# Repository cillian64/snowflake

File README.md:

# Snowflake: David's "Yuletronics" project.

A christmas decoration shaped like a snowflake, with beautiful white LEDs.
Also the most ridiculously shaped PCB I've ever had made.

Uses the TI TLV61220 boost SMPS controller to generate 5V from a single
alkaline cell.  Alternatively powered via MicroUSB-B.  Controlled by STM32F042,
programmed using TagConnect SWD or USB DFU.

Based on [Adam Greig's Christmas
Tree](https://github.com/adamgreig/yuletronics/)

Made in [KiCAD 4.0.4](http://kicad-pcb.org/).

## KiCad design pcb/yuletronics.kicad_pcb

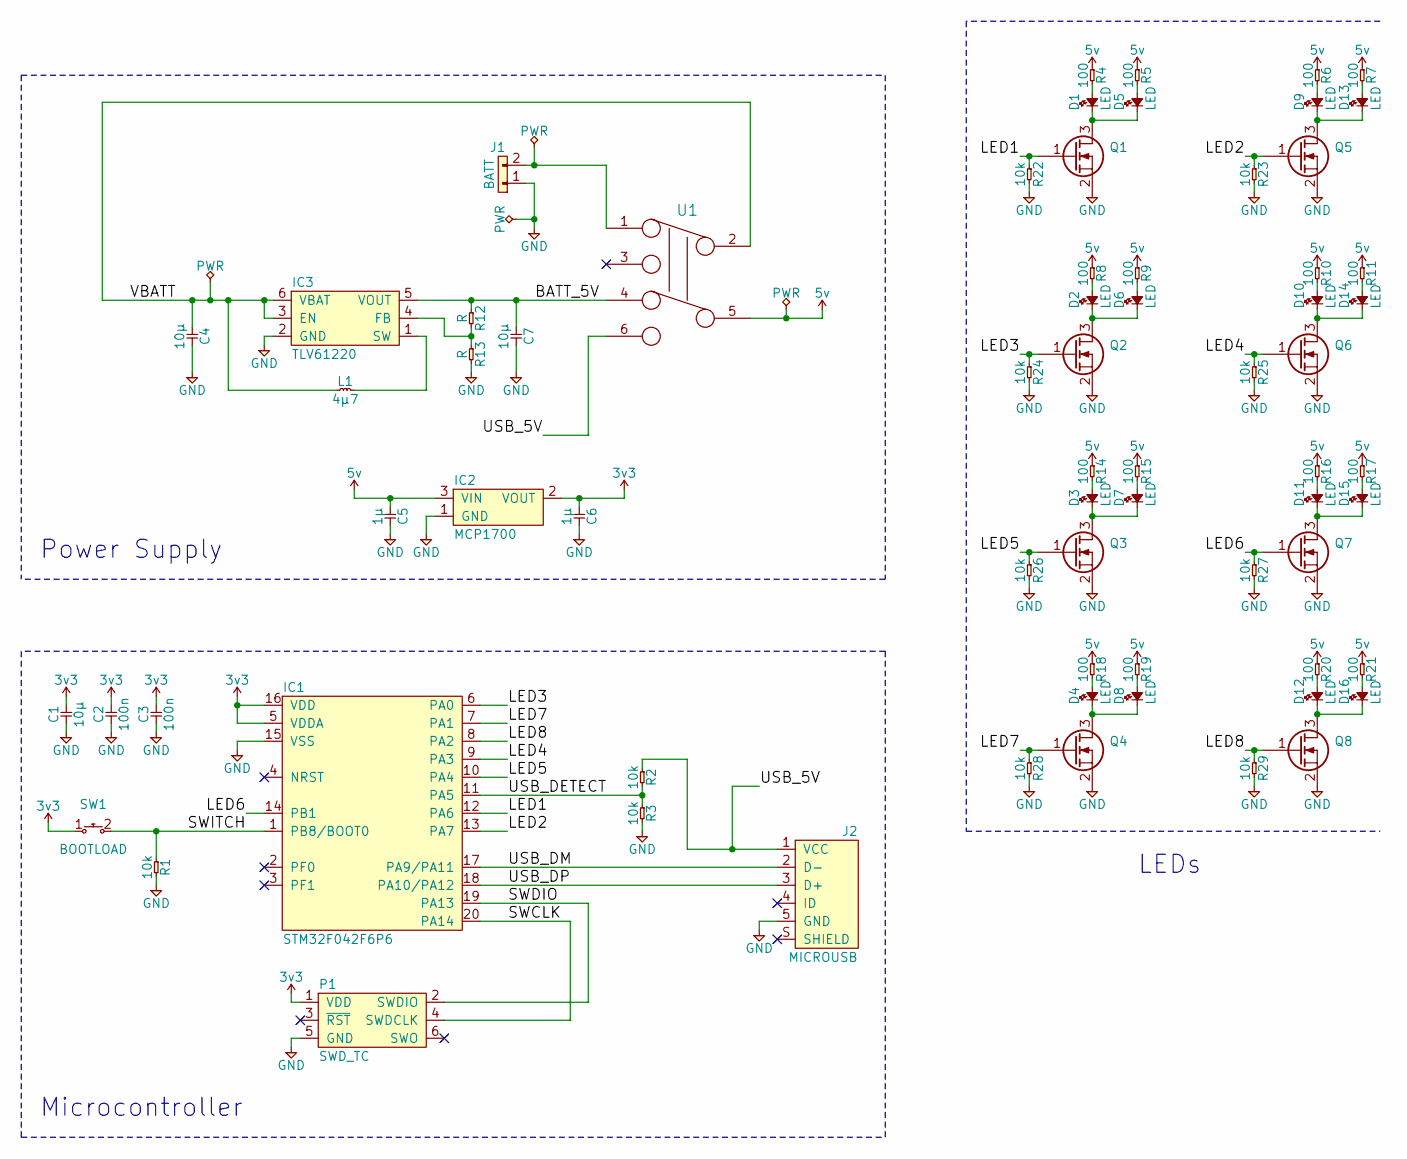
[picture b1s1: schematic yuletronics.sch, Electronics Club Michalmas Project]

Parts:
C1, C4, C7: 10µ; 0805; Farnell 2320851
C2, C3: 100n; 0805; Farnell 1759265
C5, C6: 1µ; 0805; Farnell 2320853
D1, D2, D3, D4, D5, D6, D7, D8, D9, D10, D11, D12, D13, D14, D15, D16: LED; 0805-LED; Farnell 1716764
IC1: STM32F042F6P6; TSSOP-20; Farnell 2469549
IC2: MCP1700; SOT-23; Farnell 1296592
IC3: TLV61220; SOT-23-6; Farnell 2323546
J1: BATT; AAA_HOLDER; Farnell 1702632
J2: MICROUSB; MICROUSB_MOLEX_47589-0001; Farnell 1568023
L1: 4µ7; 2016M; Farnell 2616849
P1: SWD_TC; TC2030-NL
Q1, Q2, Q3, Q4, Q5, Q6, Q7, Q8: BSS138P; SOT-23; Farnell 1859849
R1, R2, R3: 10k; 0805; Farnell 9332391
R4, R5, R6, R7, R8, R9, R10, R11, R14, R15, R16, R17, R18, R19, R20, R21: 100; 0805
R12, R13: R; 0805
R22, R23, R24, R25, R26, R27, R28, R29: 10k; 0805
SW1: BOOTLOAD; MOM_SWITCH; Farnell 2056809
U1: dpdt; Farnell 2435098

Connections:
3v3: C1.2, C2.2, C3.2, C6.1, IC1.5 (VDDA), IC1.16 (VDD), IC2.2 (VOUT), P1.1 (VDD), SW1.1
5v: C5.1, IC2.3 (VIN), R4.1, R5.1, R6.1, R7.1, R8.1, R9.1, R10.1, R11.1, R14.1, R15.1, R16.1, R17.1, R18.1, R19.1, R20.1, R21.1, U1.5
/BATT_5V: C7.1, IC3.5 (VOUT), R12.1, U1.4
/LED1: IC1.12 (PA6), Q1.1 (G), R22.1
/LED2: IC1.13 (PA7), Q5.1 (G), R23.1
/LED3: IC1.6 (PA0), Q2.1 (G), R24.1
/LED4: IC1.9 (PA3), Q6.1 (G), R25.1
/LED5: IC1.10 (PA4), Q3.1 (G), R26.1
/LED6: IC1.14 (PB1), Q7.1 (G), R27.1
/LED7: IC1.7 (PA1), Q4.1 (G), R28.1
/LED8: IC1.8 (PA2), Q8.1 (G), R29.1
/SWCLK: IC1.20 (PA14), P1.4 (SWDCLK)
/SWDIO: IC1.19 (PA13), P1.2 (SWDIO)
/SWITCH: IC1.1 (PB8/BOOT0), R1.1, SW1.2
/USB_5V: J2.1 (VCC), R2.1, U1.6
/USB_DETECT: IC1.11 (PA5), R2.2, R3.1
/USB_DM: IC1.17 (PA9/PA11), J2.2 (D-)
/USB_DP: IC1.18 (PA10/PA12), J2.3 (D+)
/VBATT: C4.1, IC3.3 (EN), IC3.6 (VBAT), L1.1, U1.2
GND: C1.1, C2.1, C3.1, C4.2, C5.2, C6.2, C7.2, IC1.15 (VSS), IC2.1 (GND), IC3.2 (GND), J1.1, J2.5 (GND), P1.5 (GND), Q1.2 (S), Q2.2 (S), Q3.2 (S), Q4.2 (S), Q5.2 (S), Q6.2 (S), Q7.2 (S), Q8.2 (S), R1.2, R3.2, R13.2, R22.2, R23.2, R24.2, R25.2, R26.2, R27.2, R28.2, R29.2
unnamed: D1.1, D5.1, Q1.3 (D)
unnamed: D1.2, R4.2
unnamed: D2.1, D6.1, Q2.3 (D)
unnamed: D2.2, R8.2
unnamed: D3.1, D7.1, Q3.3 (D)
unnamed: D3.2, R14.2
unnamed: D4.1, D8.1, Q4.3 (D)
unnamed: D4.2, R18.2
unnamed: D5.2, R5.2
unnamed: D6.2, R9.2
unnamed: D7.2, R15.2
unnamed: D8.2, R19.2
unnamed: D9.2, R6.2
unnamed: D10.1, D14.1, Q6.3 (D)
unnamed: D10.2, R10.2
unnamed: D11.1, D15.1, Q7.3 (D)
unnamed: D11.2, R16.2
unnamed: D12.1, D16.1, Q8.3 (D)
unnamed: D12.2, R20.2
unnamed: D9.1, D13.1, Q5.3 (D)
unnamed: D13.2, R7.2
unnamed: D14.2, R11.2
unnamed: D15.2, R17.2
unnamed: D16.2, R21.2
unnamed: IC3.1 (SW), L1.2
unnamed: IC3.4 (FB), R12.2, R13.1
unnamed: J1.2, U1.1

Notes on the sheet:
Power Supply
Microcontroller
LEDs

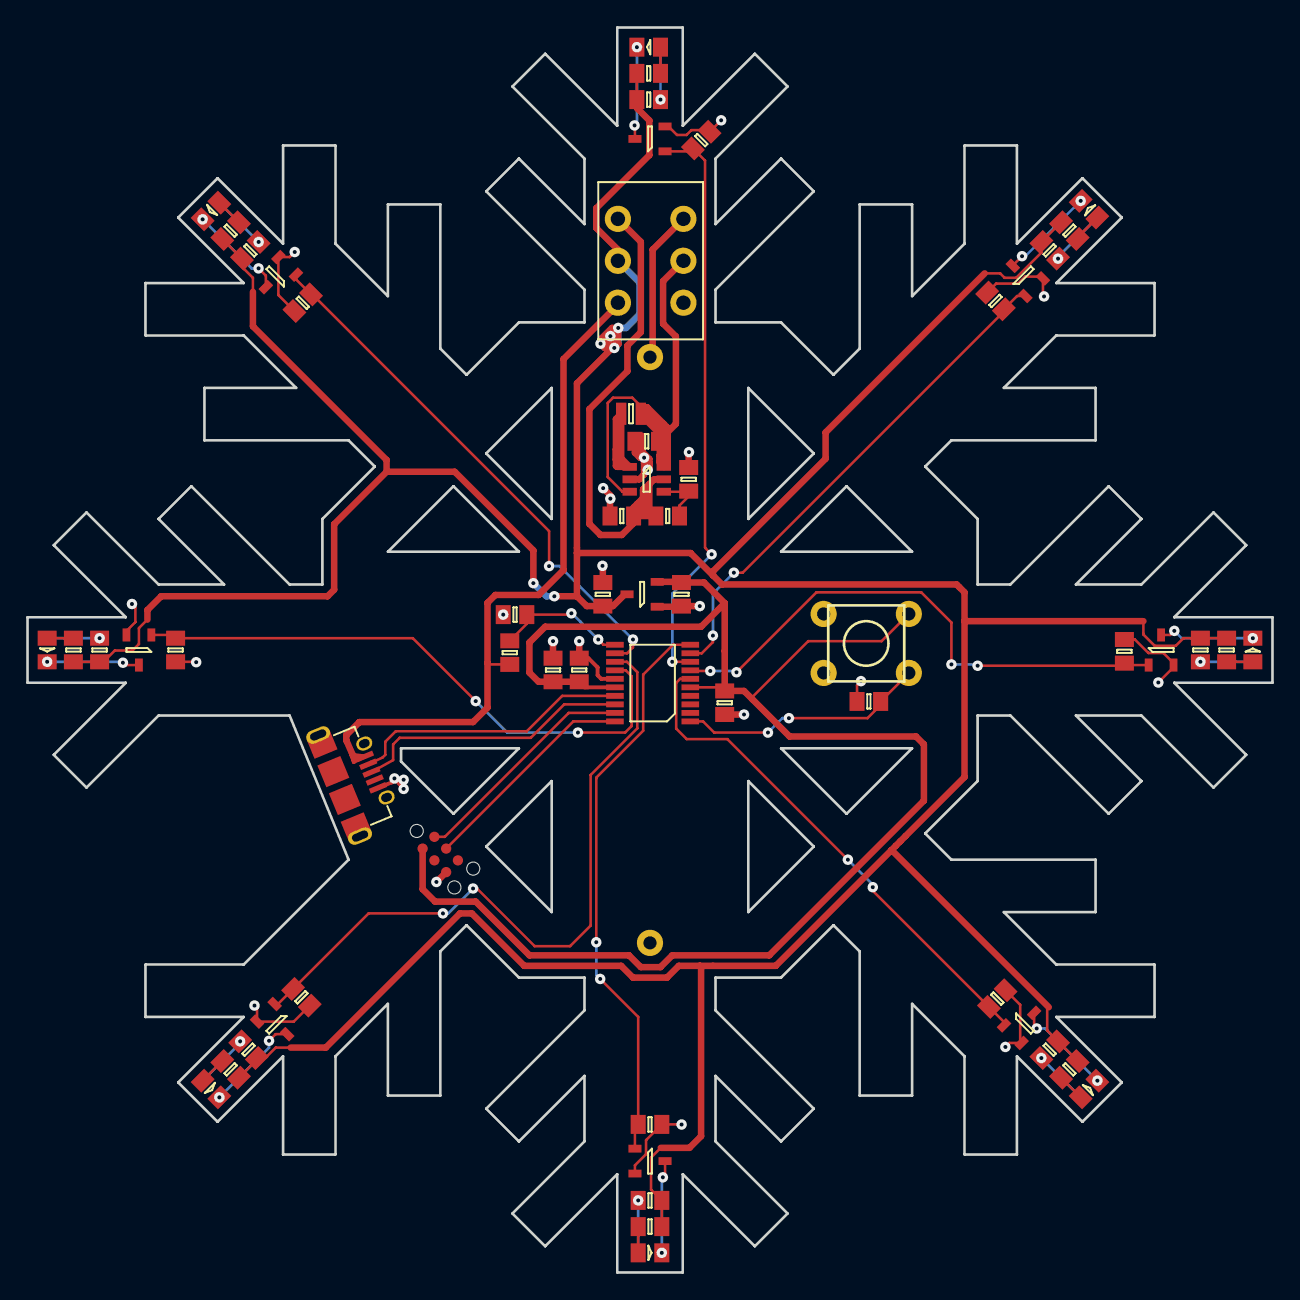
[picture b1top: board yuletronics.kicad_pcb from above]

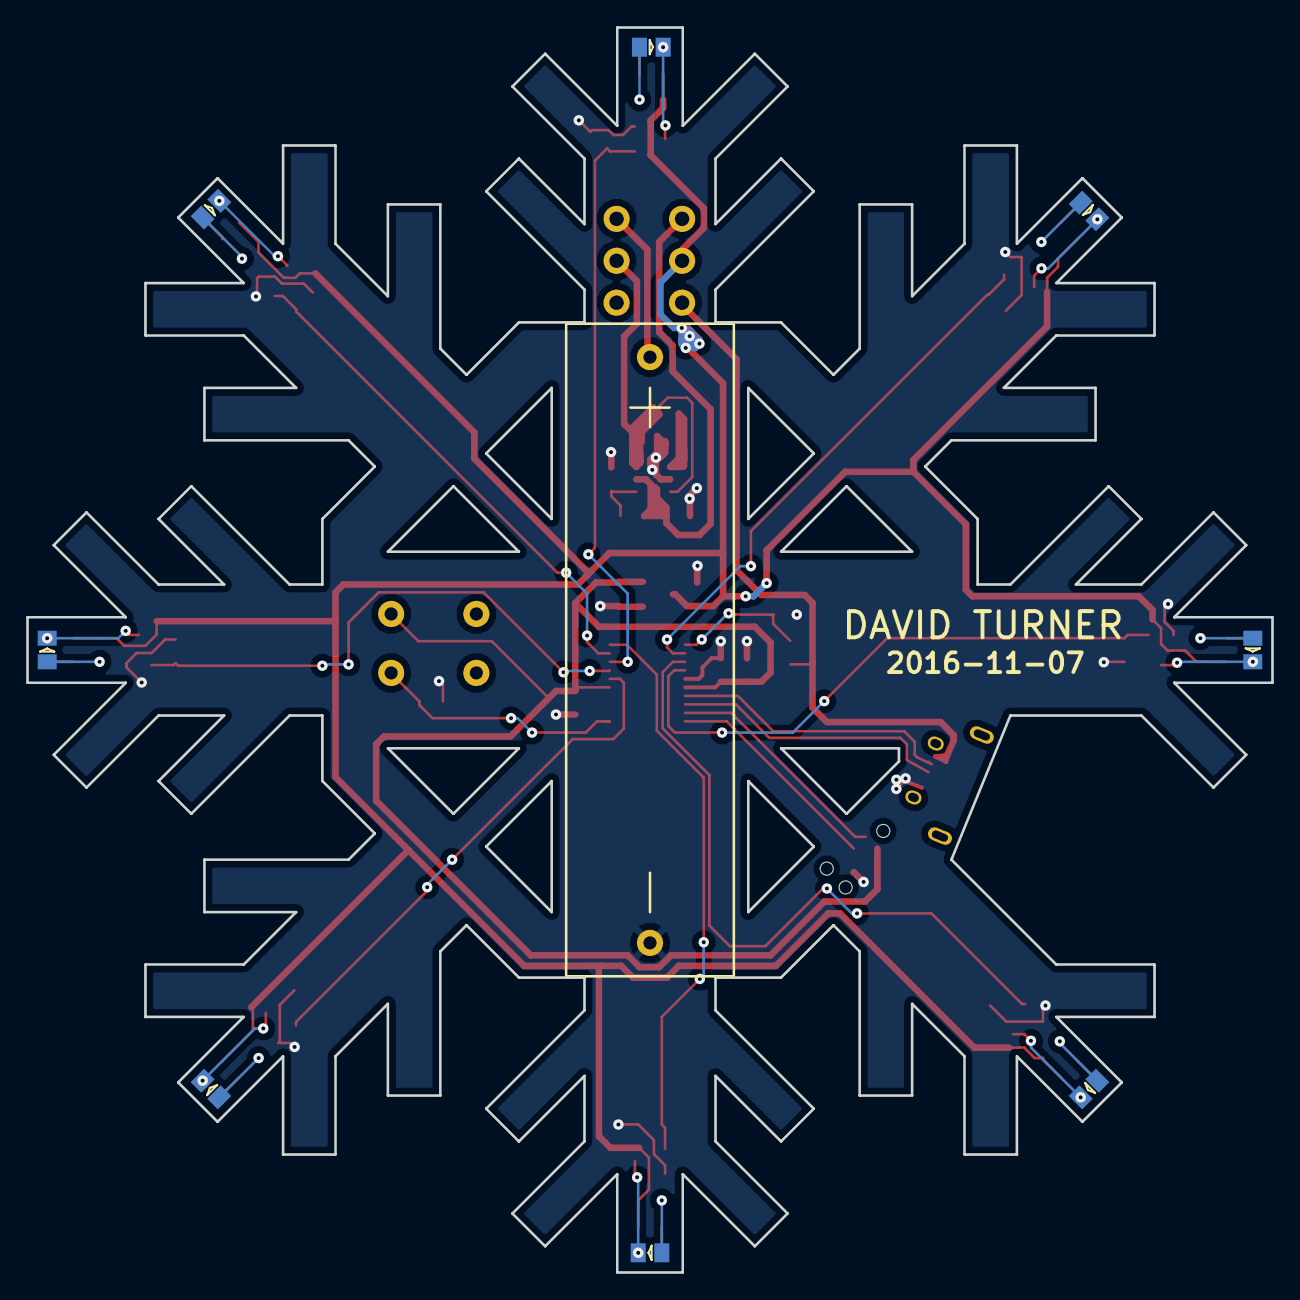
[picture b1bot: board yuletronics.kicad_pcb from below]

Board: 2 copper layers, 95.0 x 95.0 mm, 69 parts (9 on the bottom side), 47 nets.

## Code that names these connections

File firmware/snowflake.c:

#include <stdint.h>
#include <stdbool.h>

#include <libopencm3/cm3/nvic.h>
#include <libopencm3/stm32/rcc.h>
#include <libopencm3/stm32/gpio.h>
#include <libopencm3/stm32/timer.h>
#include <libopencm3/stm32/pwr.h>
#include <libopencm3/stm32/iwdg.h>

#define LED1 GPIO0
#define LED2 GPIO1
#define LED3 GPIO2
#define LED4 GPIO3
#define LED5 GPIO4
#define LED6 GPIO6
#define LED7 GPIO7
#define LED8 GPIO1

#define LED1_PORT GPIOA
#define LED2_PORT GPIOA
#define LED3_PORT GPIOA
#define LED4_PORT GPIOA
#define LED5_PORT GPIOA
#define LED6_PORT GPIOA
#define LED7_PORT GPIOA
#define LED8_PORT GPIOB

static const uint16_t led_pins[] = {
    0,
    LED1, LED2, LED3, LED4, LED5, LED6, LED7, LED8
};

static const uint32_t led_ports[] = {
    0,
    LED1_PORT, LED2_PORT, LED3_PORT, LED4_PORT,
    LED5_PORT, LED6_PORT, LED7_PORT, LED8_PORT
};

#define TURNON(led) gpio_set(led_ports[led], led_pins[led])
#define TURNOFF(led) gpio_clear(led_ports[led], led_pins[led])

//#define RTC_BKP0R MMIO32(RTC_BASE + 0x50)
#define RTC_BKP0R MMIO32(0x40002860)

#define SCB_SCR MMIO32(SCB_BASE + 0x10)
#define SCB_SCR_SLEEPDEEP (1<<2)

static void gpio_setup(void)
{
    int led;

    rcc_periph_clock_enable(RCC_GPIOA);
    rcc_periph_clock_enable(RCC_GPIOB);

    for(led=1; led<=8; led++) {
        gpio_clear(led_ports[led], led_pins[led]);
        gpio_mode_setup(
            led_ports[led], GPIO_MODE_OUTPUT, GPIO_PUPD_NONE, led_pins[led]);
        gpio_set_output_options(
            led_ports[led], GPIO_OTYPE_PP, GPIO_OSPEED_LOW, led_pins[led]);
    }
}

void tim14_isr(void)
{
    // Clear interrupt flag
    TIM_SR(TIM14) &= ~TIM_SR_UIF;
}

static void shortwait(void)
{
    // About 0.25ms
    timer_set_period(TIM14, 1);
    timer_enable_counter(TIM14);
    SCB_SCR &= ~SCB_SCR_SLEEPDEEP;
    __asm__("wfi");
    timer_disable_counter(TIM14);
}

static void standby(void)
{
    SCB_SCR |= SCB_SCR_SLEEPDEEP;
    pwr_set_standby_mode();
    __asm__("wfi");
}

int main(void)
{
    gpio_setup();

    // Setup TIM14 for sleep wakeups
    rcc_periph_clock_enable(RCC_TIM14);
    timer_reset(TIM2);
    timer_set_mode(TIM14, TIM_CR1_CKD_CK_INT, TIM_CR1_CMS_EDGE,
                   TIM_CR1_DIR_UP);
    // PCLK is running at 8MHz from HSI
    // Prescaler: divide by 2000 for timer at ~4kHz
    timer_set_prescaler(TIM14, 1999u);
    nvic_enable_irq(NVIC_TIM14_IRQ);
    timer_enable_irq(TIM14, TIM_DIER_UIE);
    timer_enable_update_event(TIM14);
    timer_disable_counter(TIM14);

    rcc_periph_clock_enable(RCC_PWR);
    rcc_periph_clock_enable(RCC_RTC);
    pwr_disable_backup_domain_write_protect();

    iwdg_reset();

    if(RTC_BKP0R > 7)
        RTC_BKP0R = 0;

    switch(RTC_BKP0R)
    {
        case 0:
            TURNON(1);
            shortwait();
            TURNOFF(1);
            break;
        case 1:
            TURNON(4);
            shortwait();
            TURNOFF(4);
            break;
        case 2:
            TURNON(6);
            shortwait();
            TURNOFF(6);
            break;
        case 3:
            TURNON(2);
            shortwait();
            TURNOFF(2);
            break;
        case 4:
            TURNON(8);
            shortwait();
            TURNOFF(8);
            break;
        case 5:
            TURNON(5);
            shortwait();
            TURNOFF(5);
            break;
        case 6:
            TURNON(7);
            shortwait();
            TURNOFF(7);
            break;
        case 7:
            TURNON(3);
            shortwait();
            TURNOFF(3);
            break;
    }

    RTC_BKP0R += 1;
    if(RTC_BKP0R == 8)
        RTC_BKP0R = 0;

    iwdg_reset();
    iwdg_set_period_ms(100);
    iwdg_start();
    standby();

    return 0;
}

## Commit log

2016-10-20 snowflake readme!
2016-10-20 More LEDs, MOSFETs, board outline
2016-11-02 Partially did new 5V bus
2016-11-02 Added FET pulldowns, placed and routed
2016-11-02 ERC/DRC
2016-11-07 Moved resistors to front, LEDs to edge
2016-11-07 gerbers
2016-11-07 updated gerber zip
2016-11-07 Changed edge cuts to add space for usb connector
2016-11-23 Added stencil, SMPS R values/parts
2016-11-23 added gif
2016-11-23 pcb renders
2016-11-30 Firmware initial commit
2016-11-30 more reasonable firmware
2016-11-30 updated stickerbom
2016-12-02 increased led hold time for bolder flash
2016-12-05 Updated BOM
2016-12-17 New low power mode
2016-12-17 Even lower power mode using standby
2016-12-23 Removed switches and USB
2016-12-23 Changed uc to STM32F030F4 TSSOP20
2017-03-13 snowflake BOM
